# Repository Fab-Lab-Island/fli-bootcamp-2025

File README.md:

Síða

# Welcome to MkDocs

For full documentation visit [mkdocs.org](https://www.mkdocs.org).

## Commands

* `mkdocs new [dir-name]` - Create a new project.
* `mkdocs serve` - Start the live-reloading docs server.
* `mkdocs build` - Build the documentation site.
* `mkdocs -h` - Print help message and exit.

## Project layout

    mkdocs.yml    # The configuration file.
    docs/
        index.md  # The documentation homepage.
        ...       # Other markdown pages, images and other files.

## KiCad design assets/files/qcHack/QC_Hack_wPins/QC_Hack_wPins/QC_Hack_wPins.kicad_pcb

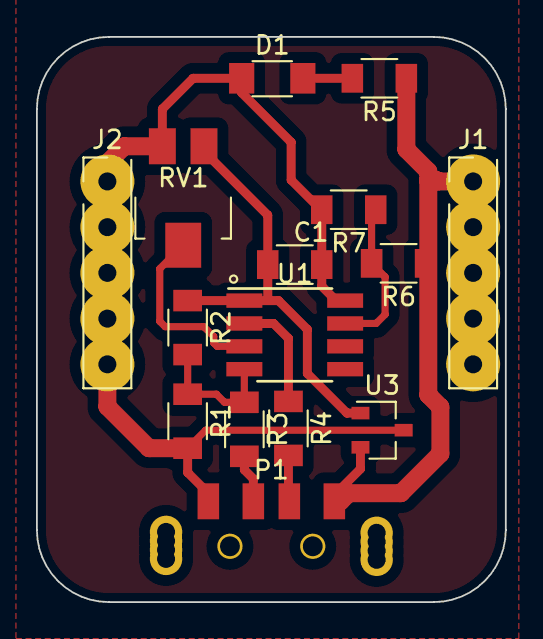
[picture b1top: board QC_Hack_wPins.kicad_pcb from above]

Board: 2 copper layers, 26.1 x 31.4 mm, 15 parts (0 on the bottom side), 10 nets.

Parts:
C1: 1µF-10µF; C_1206
D1: LED; LED_1206
J1, J2: PinHeader_01x05_P2.54mm_Vertical_THT_D1mm
P1: Conn_USB_A_Plug
R1: 2.2k; R_1206
R2, R5: 10k; R_1206
R3, R4: 1k; R_1206
R6: 47k; R_1206
R7: 4.7k; R_1206
RV1: R_POT_10K_Trimmer; Potentiometer_TT_Model-23_4.5x5.0x3.0mm
U1: ATtiny412-SS; SOIC-8_3.9x4.9mm_P1.27mm
U3: lm3480-3.3; SOT-23-3

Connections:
+3.3V: C1.1, R2.1, RV1.3, U1.1 (VCC), U3.1 (VO)
D+: R1.1, R2.2, R3.1, U1.4 (PA1)
D-: R4.1, U1.2 (DAC)
GND: C1.2, D1.1 (K), J2.1, J2.2, J2.3, J2.4, J2.5, P1.4 (GND), R1.2, R7.2, RV1.1, U1.8 (GND), U3.3 (GND)
unnamed: D1.2 (A), R5.2
unnamed: P1.3 (D+), R3.2
unnamed: P1.2 (D-), R4.2
REG: RV1.2, U1.3 (PA7)
SENSE: R6.2, R7.1, U1.7 (PA3)
VBUS: J1.1, J1.2, J1.3, J1.4, J1.5, P1.1 (5V), R5.1, R6.1, U3.2 (VI)

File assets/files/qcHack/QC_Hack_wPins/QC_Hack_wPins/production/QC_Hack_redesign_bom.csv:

Designator,Footprint,Quantity,Value,LCSC Part #
C1,C_1206,1,1µF-10µF,
D1,LED_1206,1,LED,
J2,TerminalBlock_OnShore_1x02_P3.50mm_Horizontal,1,Screw_Terminal_01x02_P3.5mm,
J4,PinHeader_1x01_P2.54mm_Horizontal_SMD,1,Conn_PinHeader_1x01_P2.54mm_Horizontal_SMD,
P1,Conn_USB_A_Plug,1,Conn_USB_A_Plug,
R1,R_1206,1,2.2k,
"R2, R5",R_1206,2,10k,
"R3, R4",R_1206,2,1k,
R6,R_1206,1,47k,
R7,R_1206,1,4.7k,
RV1,Potentiometer_TT_Model-23_4.5x5.0x3.0mm,1,R_POT_10K_Trimmer,
U1,SOIC-8_3.9x4.9mm_P1.27mm,1,ATtiny412-SS,
U3,SOT-23-3,1,lm3480-3.3,

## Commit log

2025-04-23 Spuðu Árna
2025-04-23 mkdocs init.
2025-04-23 mkdocs material theme
2025-04-23 github build ci.yml added
2025-04-23 layout of the site and some content like dagskrá
2025-04-23 small tweak
2025-04-23 added fablab.is
2025-04-25 Stefán býður ykkur velkomin
2025-04-28 project mdx 20
2025-04-28 Deployed 580efaf with MkDocs version: 1.6.1
2025-05-12 git yfirferð
2025-05-12 breytingar á git yfirferð
2025-05-12 hér eru skilaboð
2025-05-12 Update dagskra.md
    Hæ, held að þetta sé komið núna, alla vega miðað við skjalið hans Stefáns Péturs. Miðað við þann 12. maí.
2025-05-12 andri test push
2025-05-12 Create Neon flex LED
    Hæ, hér er fyrsti hlekkurinn á neon flex leiðbeiningar.
2025-05-12 Rename Neon flex LED to Neon-flex-LED.md
2025-05-12 Create ad_vera_i_studi
2025-05-12 Rename ad_vera_i_studi to ad_vera_i_studi.md
2025-05-12 QC hack page buin til
2025-05-12 qc hack fix
2025-05-12 qc hack fix 2
2025-05-12 Update git-yfirferð.md
    Lagaði stafsetningu
2025-05-12 lagað format og hlekkur
2025-05-13 qc stuff
2025-05-13 Deployed 76b8726 with MkDocs version: 1.6.1
2025-05-19 Dagskrá update
2025-05-20 boocamp fyrri ára
2025-05-20 fyrir fjölmiðla
2025-05-20 breytt dagskrá
2025-05-21 test commit
2025-05-21 QC hack with pins project
2025-05-21 qc hack screw terminal full kicad
2025-05-21 ATtiny 412 Breakout programmer board
2025-05-21 húsavík location
2025-05-21 coin design
2025-05-21 myndir
2025-05-21 moving files to ´files´ folder
2025-05-21 moving qchack images
2025-05-21 adding qcHack video
2025-05-21 adding a bunch of stuff to qcHack
2025-05-21 reyna fá CSV töflu til að birtast
2025-05-21 reyna setja inn csv skrá í töflu
2025-05-21 csv tafla
2025-05-21 reyna laga csv table stuff
2025-05-21 reyna laga plugin
2025-05-21 laga myndir
2025-05-21 image caption stuff
2025-05-21 laga caption fyrir myndir
2025-05-21 git authors
2025-05-21 git authors plugin
2025-05-21 breyting test
2025-05-21 documentation coin
2025-05-21 Deployed 83f65c9 with MkDocs version: 1.6.1
2025-05-21 ci, yml and req.txt fix
2025-05-21 added mkdocs-caption
2025-05-21 yml error fix
2025-05-21 Deployed bc4f29e with MkDocs version: 1.6.1
2025-05-21 edit og hlekkur á github
2025-05-21 Deployed 126667b with MkDocs version: 1.6.1
2025-05-21 removed assets from site
2025-05-21 Deployed 028bed2 with MkDocs version: 1.6.1
2025-05-22 github info
2025-05-22 Smá meira
2025-05-22 Deployed fc246bd with MkDocs version: 1.6.1
2025-05-22 look at this
2025-05-22 Deployed 2a70bf1 with MkDocs version: 1.6.1
2025-05-22 Deployed 13248a6 with MkDocs version: 1.6.1
2025-05-22 Deployed 9d34d69 with MkDocs version: 1.6.1
2025-05-22 Thursday heading
2025-05-22 Deployed 9a153ea with MkDocs version: 1.6.1
2025-05-22 ATtiny412 breakout site
2025-05-22 Deployed 9f6aa2a with MkDocs version: 1.6.1
2025-05-22 ATtiny412 bretti
2025-05-22 Deployed 3c96c4b with MkDocs version: 1.6.1
2025-05-22 caption fix
2025-05-22 Deployed 2c7b5b7 with MkDocs version: 1.6.1
2025-05-22 ATtiny412 bretti með Serial pinnum
2025-05-22 Deployed 4cd57eb with MkDocs version: 1.6.1
2025-05-22 dagskra
2025-05-22 Deployed f9f7f9e with MkDocs version: 1.6.1
2025-05-22 news day 1
2025-05-22 Deployed 17fb8fa with MkDocs version: 1.6.1
2025-05-22 ATtiny412 bretti með Serial pinnum bretti
2025-05-22 Deployed 2e2c5d1 with MkDocs version: 1.6.1
2025-05-22 ATtiny412 bretti með Serial pinnum bretti laga mynd
2025-05-22 adding users to document instructions
2025-05-22 Deployed 3a3238a with MkDocs version: 1.6.1
2025-05-22 Deployed 22e4c58 with MkDocs version: 1.6.1
2025-05-22 3d malm
2025-05-22 malm 3d content
2025-05-22 Deployed 1a9b90f with MkDocs version: 1.6.1
2025-05-22 mdx 20
2025-05-22 Deployed 3aa5a0b with MkDocs version: 1.6.1
2025-05-23 Kynning grodurhus.md
2025-05-23 Deployed d37f6cb with MkDocs version: 1.6.1
2025-05-23 Deployed 3b2f756 with MkDocs version: 1.6.1
2025-05-23 Create Eddan_3Dscan.md
    eddan skönnun
2025-05-23 Deployed 490d67c with MkDocs version: 1.6.1
2025-05-23 added image
2025-05-23 Deployed 7d1f850 with MkDocs version: 1.6.1
2025-05-23 add images
2025-05-23 Deployed 51e7fb6 with MkDocs version: 1.6.1
2025-05-23 Deployed ecd46da with MkDocs version: 1.6.1
2025-05-23 fix images
2025-05-23 Deployed c195b8e with MkDocs version: 1.6.1
2025-05-23 fix text
2025-05-23 Deployed c8b6403 with MkDocs version: 1.6.1
2025-05-23 myndir photos tab
2025-05-23 Deployed 629b90d with MkDocs version: 1.6.1
2025-05-23 add link
2025-05-23 Deployed 14f56fc with MkDocs version: 1.6.1
2025-05-23 Eink
2025-05-23 Deployed faaf5fb with MkDocs version: 1.6.1
2025-05-23 fix link
2025-05-23 Deployed a5e289e with MkDocs version: 1.6.1
2025-05-23 epaper linkar
2025-05-23 Deployed 2d11607 with MkDocs version: 1.6.1
2025-05-23 fixing link again
2025-05-23 Deployed aa944f2 with MkDocs version: 1.6.1
2025-05-23 fix link 3
2025-05-23 Deployed 4b9a186 with MkDocs version: 1.6.1
2025-05-23 markdown leiðbeiningar
2025-05-23 Deployed ccaa5c1 with MkDocs version: 1.6.1
2025-05-23 toc settup and small adjustments
2025-05-23 Deployed cecc9e2 with MkDocs version: 1.6.1
2025-05-23 drykkir dagskra.md
2025-05-23 Deployed d1866c1 with MkDocs version: 1.6.1
2025-05-23 Deployed 854d6b2 with MkDocs version: 1.6.1
2025-05-23 Deployed 57cc15b with MkDocs version: 1.6.1
2025-05-23 Deployed 334e0ca with MkDocs version: 1.6.1
2025-05-23 Deployed afc0d91 with MkDocs version: 1.6.1
2025-05-23 Deployed f794dd0 with MkDocs version: 1.6.1
2025-05-23 Deployed 6c1419a with MkDocs version: 1.6.1
2025-05-23 Deployed 70ac5eb with MkDocs version: 1.6.1
2025-05-23 Deployed 0c70881 with MkDocs version: 1.6.1
2025-05-23 Deployed 8afd2f0 with MkDocs version: 1.6.1
2025-05-23 Deployed f3aeba3 with MkDocs version: 1.6.1
2025-05-23 Deployed 5b621ec with MkDocs version: 1.6.1
2025-05-23 Deployed 7ae9fd0 with MkDocs version: 1.6.1
2025-05-23 Deployed 91fc9f1 with MkDocs version: 1.6.1
2025-05-23 Deployed 873b01d with MkDocs version: 1.6.1
2025-05-23 Deployed fa1cc4c with MkDocs version: 1.6.1
2025-05-23 Create sarah and alissa
2025-05-23 Deployed db7d27b with MkDocs version: 1.6.1
2025-05-23 Deployed 4ea00d8 with MkDocs version: 1.6.1
2025-05-23 Deployed 5907f53 with MkDocs version: 1.6.1
2025-05-23 Deployed 29be90f with MkDocs version: 1.6.1
2025-05-23 documentation coin files
2025-05-23 Deployed 0221917 with MkDocs version: 1.6.1
2025-05-23 Deployed 391da07 with MkDocs version: 1.6.1
2025-05-23 Deployed d456b49 with MkDocs version: 1.6.1
2025-05-23 Deployed 402b46b with MkDocs version: 1.6.1
2025-05-23 Deployed 39c9c9f with MkDocs version: 1.6.1
2025-05-23 Deployed 41f570c with MkDocs version: 1.6.1
2025-05-23 qcHack with sidepins
2025-05-23 Deployed 8d64ff9 with MkDocs version: 1.6.1
2025-05-23 minimal rp2040
2025-05-23 Deployed 3e802bd with MkDocs version: 1.6.1
2025-05-23 Deployed 9d30571 with MkDocs version: 1.6.1
2025-05-26 index page and dagskrá cleen up
2025-05-26 Deployed df744bd with MkDocs version: 1.6.1
2025-05-26 Sewing machine
2025-05-26 Deployed 60f7bc8 with MkDocs version: 1.6.1
2025-05-26 Saumavél
2025-05-26 Deployed 3072826 with MkDocs version: 1.6.1
2025-05-26 Converting line to satin
2025-05-26 Deployed 4ab8505 with MkDocs version: 1.6.1
2025-05-27 Params
2025-05-27 Deployed cf784d9 with MkDocs version: 1.6.1
2025-05-27 Finished documenting in english
2025-05-27 Unnið að íslenska textanum
2025-05-27 Deployed 7b8dc5f with MkDocs version: 1.6.1
2025-05-27 Íslenskan komin inn
2025-05-27 Deployed 641cd8f with MkDocs version: 1.6.1
2025-05-27 Small adjustments
2025-05-27 Deployed aaac2ea with MkDocs version: 1.6.1
2025-05-27 Headings
2025-05-27 Deployed 54ffb1d with MkDocs version: 1.6.1
2025-05-27 Two hashtags
2025-05-27 Deployed 3d84ee7 with MkDocs version: 1.6.1
2025-05-27 Paralell
2025-05-27 Deployed b6a7fdf with MkDocs version: 1.6.1
2025-05-28 adding an embroidry page
2025-05-28 Deployed 01f8625 with MkDocs version: 1.6.1
2025-05-28 editing embroidery page
2025-05-28 Deployed 02ff56a with MkDocs version: 1.6.1
2025-05-28 Sko Doddi...
    ég er líka hérna
2025-05-28 Deployed 485b49e with MkDocs version: 1.6.1
2025-05-28 Create Gluggafraesun-grodurhus.md
    Gluggafræsun md
2025-05-28 Deployed f2670a2 with MkDocs version: 1.6.1
2025-05-29 add img for the embroidery page
2025-05-29 Deployed 8863e6e with MkDocs version: 1.6.1
2025-05-29 edits to embroidery
2025-05-29 Deployed f1668f0 with MkDocs version: 1.6.1
2025-05-29 adding example file to the embroidery
2025-05-29 Deployed 7df29af with MkDocs version: 1.6.1
2025-05-29 edits to the embroidery file
2025-05-29 Deployed c3fe106 with MkDocs version: 1.6.1
2025-05-29 rename the file for the embroidery
2025-05-29 Deployed b4a451f with MkDocs version: 1.6.1
2025-05-29 final commit for now on the embroidry
2025-05-29 Deployed be25272 with MkDocs version: 1.6.1
2025-05-30 Laga listann
2025-05-30 Deployed 9f24623 with MkDocs version: 1.6.1
2025-05-31 Text copied from Embroidery and Inkstitch and changed the name to Embroidery and Inkstitch_moved. Now all text is under Embroidery and Inkstitch under Verkefnavinna
2025-05-31 Deployed 8c5c292 with MkDocs version: 1.6.1
2025-06-23 news item about neil
2025-06-23 Deployed e3471d1 with MkDocs version: 1.6.1
2025-06-24 updated neil post
2025-06-24 Deployed f9f3c37 with MkDocs version: 1.6.1
2025-06-24 fixed link to avatar image
2025-06-24 Deployed 2ac0062 with MkDocs version: 1.6.1
2025-06-24 neil post text edit
2025-06-24 Deployed 01b516c with MkDocs version: 1.6.1
2025-06-24 malmprentun edit
2025-06-24 Deployed e35a4be with MkDocs version: 1.6.1
2025-06-24 tiny edit to neil story
2025-06-24 Deployed 6cfd79b with MkDocs version: 1.6.1
2025-10-08 laser
2025-10-08 Deployed 9f66722 with MkDocs version: 1.6.1
